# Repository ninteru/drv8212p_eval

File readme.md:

# DRV8212P Evaluation Breakout Board

This board was created to evaluate the operation of the [TI DRV8212P](https://www.ti.com/product/DRV8212P) in driving common N20 geared DC motors.

Certain considerations are required dependent on the selected motor and sensing features. By default, the `VM (V_motor)` and `VCC (V_io)` are tied together via the bridged pad. This is for operation of the motor at the same voltage of the controller mcu. If independent nets are to be used, the bridge must be cut and `VM` and `VCC` must be independently provided via the input header pins.

Additionally, DRV8212P provides load sensing capability via a sense resistor between the ICs ground and the board ground. The value of R_SENSE is dependent on the requirements of your application and is left to the user to calculate.

## Calculating R_SENSE

## Schematic

## PCB Layout

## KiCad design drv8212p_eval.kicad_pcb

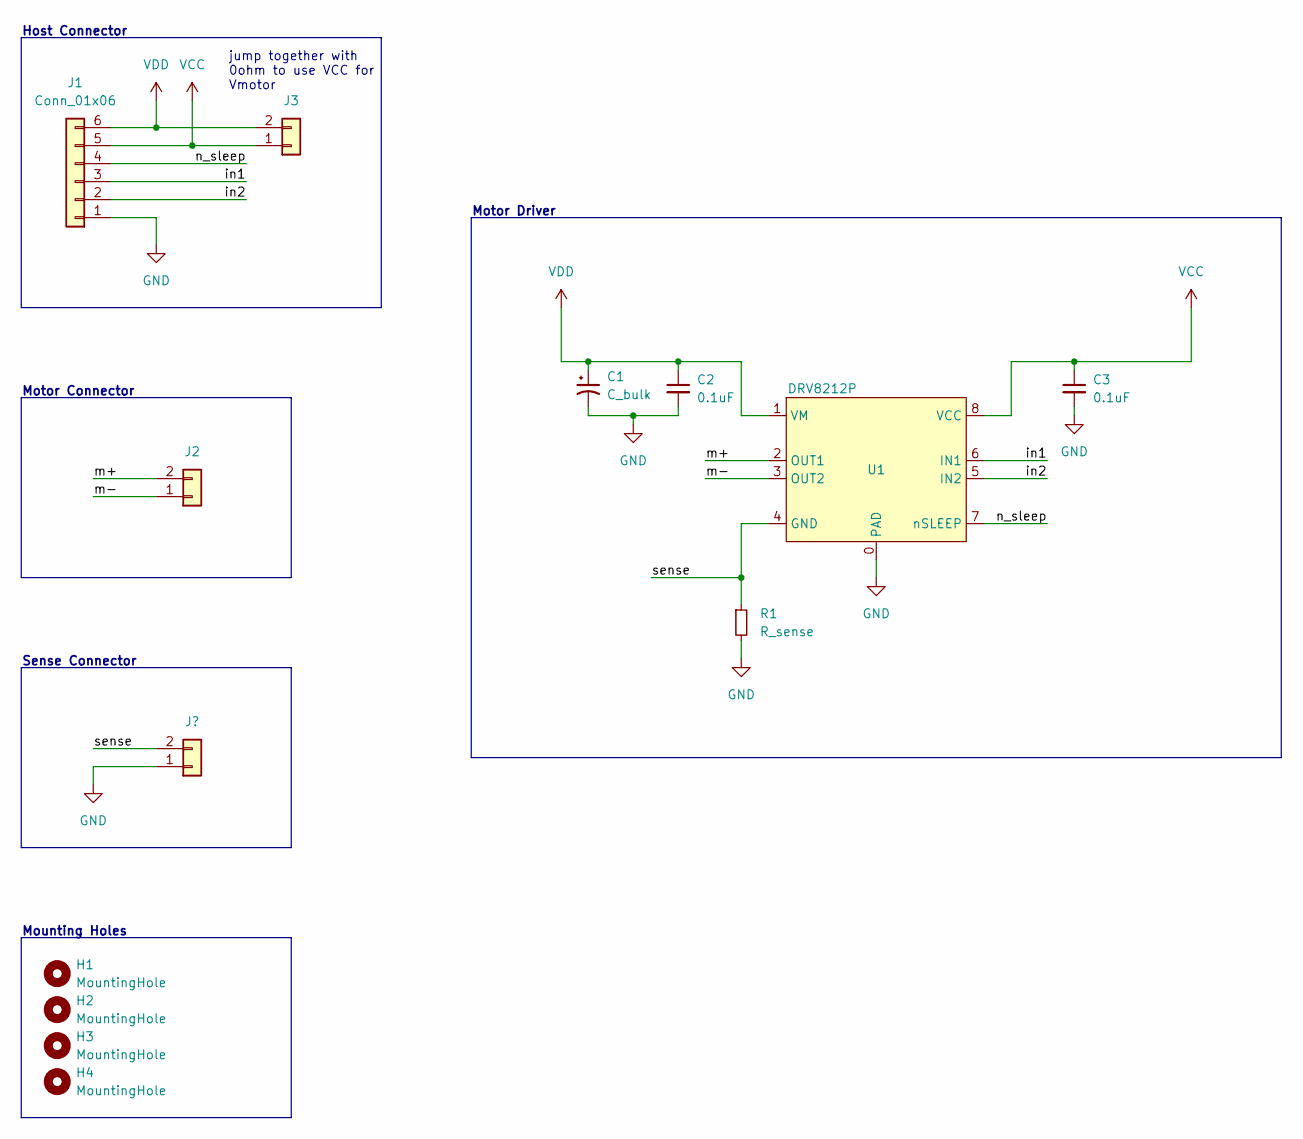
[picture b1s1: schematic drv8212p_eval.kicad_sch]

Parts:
C1: C_bulk; C_0805_2012Metric
C2, C3: 0.1uF; C_0805_2012Metric
H1, H2, H3, H4: MountingHole; MountingHole_2.2mm_M2_Pad
J1: Conn_01x06; PinHeader_1x06_P2.54mm_Vertical
J2: Conn_01x02; PinHeader_1x02_P2.54mm_Vertical
J3: Conn_01x02; SolderJumper-2_P1.3mm_Bridged_RoundedPad1.0x1.5mm
R1: R_sense; R_0805_2012Metric
U1: DRV8212P

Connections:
/in1: J1.3, U1.6 (IN1)
/in2: J1.2, U1.5 (IN2)
/m+: J2.2, U1.2 (OUT1)
/m-: J2.1, U1.3 (OUT2)
/n_sleep: J1.4, U1.7 (nSLEEP)
/sense: R1.1, U1.4 (GND); also elsewhere on the board
GND: C1.2, C2.2, C3.2, J1.1, R1.2, U1.0 (PAD); also elsewhere on the board
VCC: C3.1, J1.5, J3.1, U1.8 (VCC)
VDD: C1.1, C2.1, J1.6, J3.2, U1.1 (VM)

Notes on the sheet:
Motor Driver
Motor Connector
Host Connector
jump together with 0ohm to use VCC for Vmotor
Sense Connector
Mounting Holes

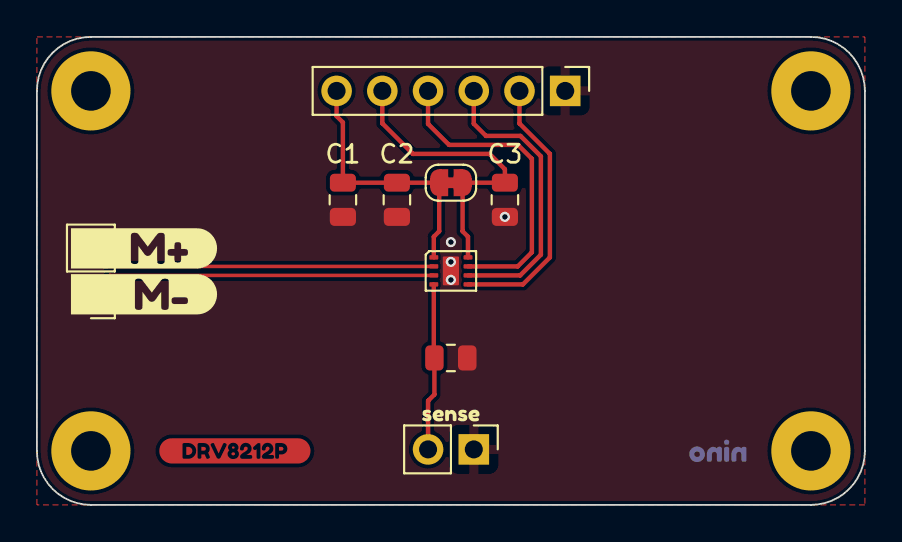
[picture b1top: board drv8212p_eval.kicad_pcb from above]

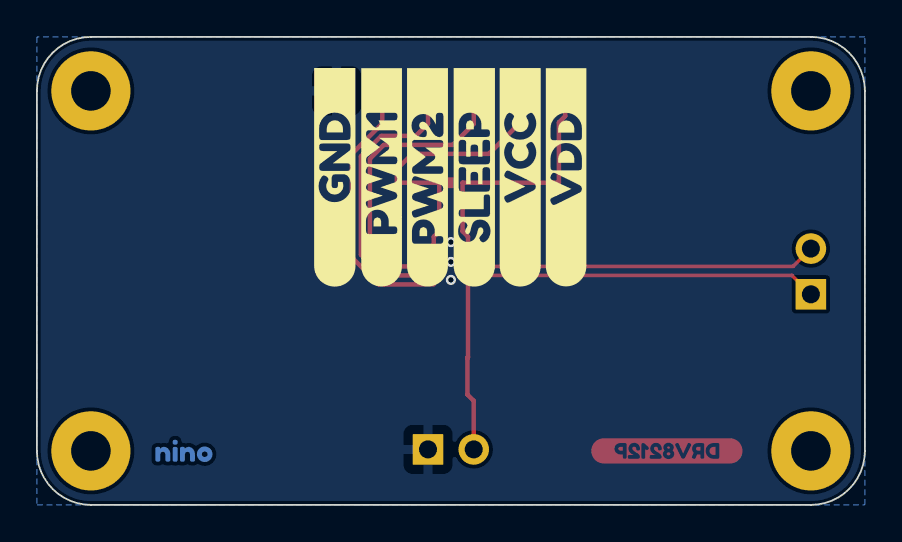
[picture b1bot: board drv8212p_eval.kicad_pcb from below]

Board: 2 copper layers, 46.0 x 26.0 mm, 24 parts (7 on the bottom side), 9 nets.

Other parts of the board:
J4: Conn_01x02; PinHeader_1x02_P2.54mm_Vertical
kibuzzard-63D75A48: G***; kibuzzard-63D75A48
kibuzzard-63D75C7D: G***; kibuzzard-63D75C7D
kibuzzard-63D75C83: G***; kibuzzard-63D75C83
kibuzzard-63D75C88: G***; kibuzzard-63D75C88
kibuzzard-63D75C91: G***; kibuzzard-63D75C91
kibuzzard-63D75C96: G***; kibuzzard-63D75C96
kibuzzard-63D75CDC: G***; kibuzzard-63D75CDC
kibuzzard-63D753DC: G***; kibuzzard-63D753DC
kibuzzard-63D75404: G***; kibuzzard-63D75404
kibuzzard-63D75466: G***; kibuzzard-63D75466
kibuzzard-63E074E8: G***; kibuzzard-63E074E8

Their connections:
/sense: J4.2; also elsewhere on the board
GND: J4.1; also elsewhere on the board

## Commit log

2023-01-31 move 3d models into folder
2023-01-31 added gitignore
2023-01-31 created readme
2023-01-31 update 3dmodel path
2023-01-31 update kicad generated ignores
2023-01-31 update kicad temp file ignore
2023-02-06 updated footprints
2023-02-06 tracked fabrication outputs
